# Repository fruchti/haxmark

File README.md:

# haxmark

This project has the goal of modifying a Lexmark E360d/E360dn for direct PCB printing.

It is based on [this](http://www.instructables.com/id/Modification-of-the-Lexmark-E260-for-Direct-Laser--1) great instructable by mlerman, which uses a Lexmark E260d. The E360d is nearly identical in its hardware. Anyhow, I found out that there are some software differences between E260d and E360d. This is why a designed a new MCU board for simulating the printer's timings.

## Project status and performance

The printer behaves reasonably predictable and the way it should. The results are quite good: A minimal trace width of 5 mil and a minimal clearance of 10 mil are no big deal.

A review of the project and some potential issues of the process in general can be found in [a blog post of mine](https://25120.org/post/haxmark/).

## Modification

### Some notes before you modify your printer

I strongly recommend that you test your printer in an unmodified state with exactly the driver and printer settings you intend to use it with to print on PCBs. I found out the hard way that the behaviour and the timing differ from driver to driver. It is definitely a good idea to make a dump of the interesting signals (operator panel line, manual paper feed sensor, paper in sensor, exit sensor) with a logic analyser to get the exact timing of your printing setup so you can adjust the timing settings in the MCU board's source code. I included a dump made with logic_sniffer and my settings. I use the printer with linux and [this](http://www.openprinting.org/printer/Lexmark/Lexmark-E360d) PPD file with 1200dpi native resolution. I have not used it with Windows, so if you plan to do that, better check the printer's behaviour in detail before making any modification.

### Differences to the E260d

The main hardware difference between E260d and E360d is the use of a different operator's panel. But in the software there seem to be quite some more:

- The E360d does not, unlike the E260d, pull in a piece of paper stuck into its front. Instead, it stops with a paper jam message.
- When starting a print, the printers motor runs for a while before it is stopped and the user has to confirm he has inserted a piece of paper into the manual feeder by pressing the tick button. Then, the motor starts running again and a few seconds later, a clutch is activated and the paper is finally pulled in. If the paper is inserted significantly before the clutch is activated, the printer reports a paper jam. Note that some drivers seem to omit the first motor running phase (this modification should work with both variants)

### Hardware modification

The hardware modifications are mainly the same as in [the original instructable](http://www.instructables.com/id/Modification-of-the-Lexmark-E260-for-Direct-Laser--1). But, because the motor directly pulls in the carrier, an additional clutch is needed to keep the rollers stopped unless the carrier actually should move. The printer provides a solenoid, which is able to block the rollers, on its left side. Cut the low-side cable at the printer's controller board and connect it to the new MCU board. Leave the other end connected to 24 V. The MCU board also needs a connection to a hall sensor of the motor in order to be able to check if it is running. I tapped the lowest pin on J17, but any of the three sensor lines should work. Just be sure that you do not connect the MCU to one of the motor windings (the three wires with the ferrite bead over them), as they are driven with 24 V.

I made some additional modifications:

- I use a 18 cm wide and 30 cm long carrier. The 60 cm long carrier proved to be way to long for me.
- I swapped the forked light barrier "new paper in sensor" for a reflective sensor (SFH900-2). This way I can use a piece of tape on the carriers bottom instead of a hole. If you use the original approach, you have to invert the signal in the AVR's source code.
- My carrier has two markings for the reflective light sensor. The new first marking triggers the sensor when the carrier is pulled in just slightly. The MCU board uses this to feed the carrier into the printer into the exact same starting position every time. Especially for double-sided PCBs this is useful as it provides better alignment. The markings on my carrier are now 113 mm and 181 mm from the top with the reflective light sensor being 100 mm in front of the first axle.

### New MCU board

My new controller board monitors the motor in addition to the tapped line from the operator panel, which by the way is a serial data line and gets toggled with every key press, at the startup and every once in a while. I also included three status LEDs, which are not really useful at the moment, and an RS232-TTL port for debugging purposes, which is unused so far. The crystal is actually optional, just make sure you change the fuse bits in the makefile if you do not solder one in.

## Printing

The printing process is straightforward:

1. Hit "Print" in whatever program you design your PCBs with
2. Wait until the printer's motor stops running
3. Put the carrier with the bare PCB on it in
4. Press the tick button on the printer and watch it print
5. Treat the PCB in acetone vapour (as described in the original instructable) and etch

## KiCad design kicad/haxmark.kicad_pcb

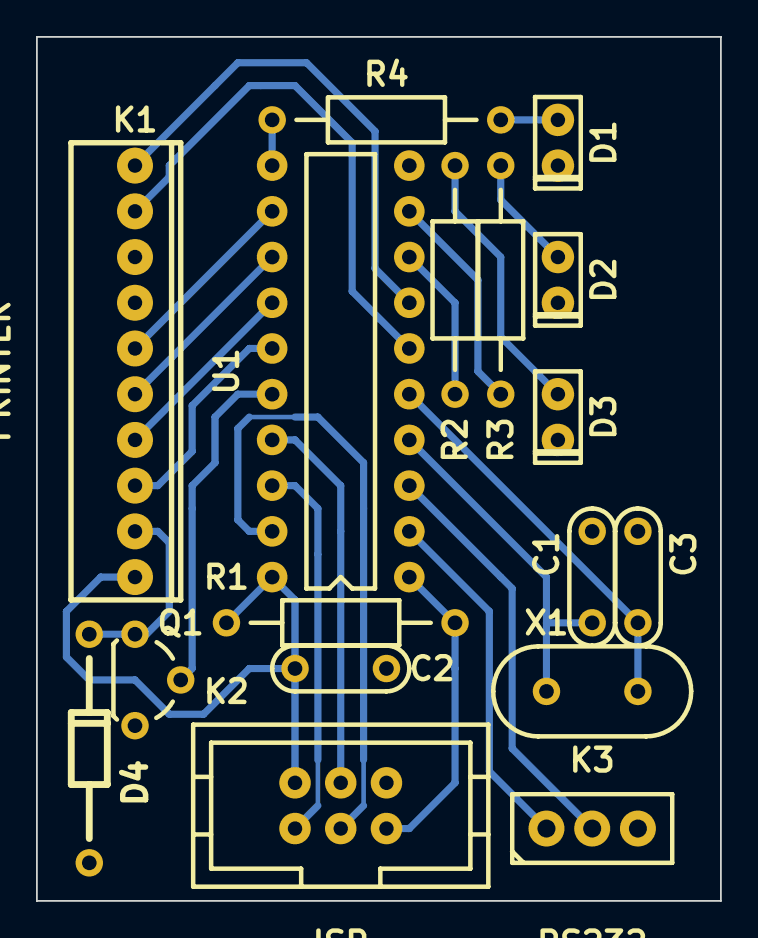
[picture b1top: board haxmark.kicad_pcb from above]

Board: 2 copper layers, 38.0 x 48.0 mm, 17 parts (0 on the bottom side), 24 nets.

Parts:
C1, C3: 22p; C_200
C2: 100n; C_200
D1: rd; LED_RECT
D2: ye; LED_RECT
D3: gn; LED_RECT
D4: 36V; DO35_500
K1: PRINTER; PSS254-10G
K2: ISP; WSL6G
K3: RS232; PINHEAD_1_3
Q1: BS170; TO92
R1: 10k; R_0207_500
R2, R3, R4: 1k; R_0207_500
U1: ATTINY2313-20PU; DIP20_300
X1: 8MHz; XTAL_200

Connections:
+5V: C2.1, K1.1, K2.2, R1.2, U1.20
/CLTCH: Q1.2, U1.16
/CLUTCH: D4.2, K1.2, Q1.1
/EXIT: K1.3, U1.15
/HALL: K1.10, U1.7
/MISO: K2.1, U1.18
/MOSI: K2.4, U1.17
/MPF: K1.4, U1.14
/NPIN: K1.6, U1.12
/OPPN: K1.9, U1.6
/PIN: K1.5, U1.13
/RESET: K2.5, R1.1, U1.1
/SCK: K2.3, U1.19
GND: C1.2, C2.2, C3.2, D1.2, D2.2, D3.2, D4.1, K1.7, K1.8, K2.6, K3.3, Q1.3, U1.10
unnamed: C1.1, U1.4, X1.2
unnamed: C3.1, U1.5, X1.1
unnamed: D1.1, R4.2
unnamed: D2.1, R3.2
unnamed: D3.1, R2.2
unnamed: K3.1, U1.2
unnamed: K3.2, U1.3
unnamed: R2.1, U1.8
unnamed: R3.1, U1.9
unnamed: R4.1, U1.11

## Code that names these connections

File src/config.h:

// -fruchti 2015

#ifndef CONFIG_H_
#define CONFIG_H_

#define F_CPU           8000000

#include <avr/io.h>
#include <avr/interrupt.h>

// Printer settings
#define PRINTRES        1200            // Resolution, either 1200 or 2400 (dpi)

// All delay times are measured in milliseconds
#define T_HALL_L        6               // Hall sensor timeout. After this time
                                        // is elapsed without a pin change, the
                                        // motor is considered stopped
#define T_POWRON        5000            // Delay to allow printer to start up

#if PRINTRES == 1200                    // Printer set to 1200dpi

#define T_CLUTCH        3559            // Delay between starting print job and
                                        // pulling in carrier/activating manual
                                        // paper feed sensor
#define T_EXIT_H        1666            // Delay between activation of paper in
                                        // and activation of exit sensor
#define T_MNPF_L        419             // Delay before deactivation of manual
                                        // paper feed sensor after exit sensor
                                        // is activated
#define T_PPIN_L        630             // Delay before deactivation of paper
                                        // in sensor
#define T_EXIT_L        1689            // Delay before deactivation of exit
                                        // sensor

#else                                   // Timing for 2400dpi image resolution
#define T_CLUTCH        3406
#define T_EXIT_H        841
#define T_MNPF_L        213
#define T_PPIN_L        311
#define T_EXIT_L        849
#endif

#define D_LED_RD        DDRD            // Red status LED
#define O_LED_RD        PORTD
#define P_LED_RD        PD6

#define D_LED_YE        DDRD            // Yellow status LED
#define O_LED_YE        PORTD
#define P_LED_YE        PD5

#define D_LED_GN        DDRD            // Green status LED
#define O_LED_GN        PORTD
#define P_LED_GN        PD4

#define I_NPPINS        PINB            // New paper in sensor
#define O_NPPINS        PORTB
#define P_NPPINS        PB0

#define D_PPINSO        DDRB            // Paper in sensor output
#define O_PPINSO        PORTB
#define P_PPINSO        PB1

#define D_MNPFSO        DDRB            // Manual paper feed sensor output
#define O_MNPFSO        PORTB
#define P_MNPFSO        PB2

#define D_EXITSO        DDRB            // Exit sensor output
#define O_EXITSO        PORTB
#define P_EXITSO        PB3

#define D_CLUTCH        DDRB            // Clutch control pin
#define O_CLUTCH        PORTB
#define P_CLUTCH        PB4

#define I_OPANEL        PIND            // Operator panel
#define P_OPANEL        PD2             // CAUTION: Do not change (INT0 is used
                                        // for monitoring this input)!

#define I_HALL_1        PIND            // Hall sensor from motor
#define P_HALL_1        PD3

#endif

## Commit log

2015-05-05 Initial
2015-05-23 Always complete sensor signal sequence when started
    I started getting paper jam errors which was likely to be caused by
    communication between printer controller board and operator's panel
    toggling the tapped data line and therefore resetting the MCU board's
    state to the idle state while printing. If the state is reset before the
    signal sequence is completed, the printer of course will not get the
    sensor signals it is expecting.
2015-05-23 Add PNG of logic analyzer dump
2015-06-11 Win7 Logic dumps added
    Pictures and CSV of logic level dumps of an unmodifed E360DN added.
    Legacy Win7 driver and Lexmark driver captured
2015-09-20 Drive clutch at startup
    Now you can directly hear if everything is working when turning the printer on.
2015-09-20 Add logic analyzer dump of 1200dpi print
2015-09-20 Adjust timing to 1200dpi
    At first I was using the 2400dpi mode of the printer. I now switched to
    the native resolution of 1200dpi because the results are way better. The
    2400dpi mode can still be used if a #define in config.h is changed.
2015-10-06 Add initial feed
    The MCU board now lets the printer pull in the carrier until the new
    paper in sensor is triggered for the first time and then starts the
    print like before. The new "initial feed" provides an alignment of the
    carrier which is exactly the same every time. Of course, the carrier now
    needs two markings.
2017-12-26 Change licence
2020-01-06 README: Fix some minor things
2020-01-06 README: Add blog post link
